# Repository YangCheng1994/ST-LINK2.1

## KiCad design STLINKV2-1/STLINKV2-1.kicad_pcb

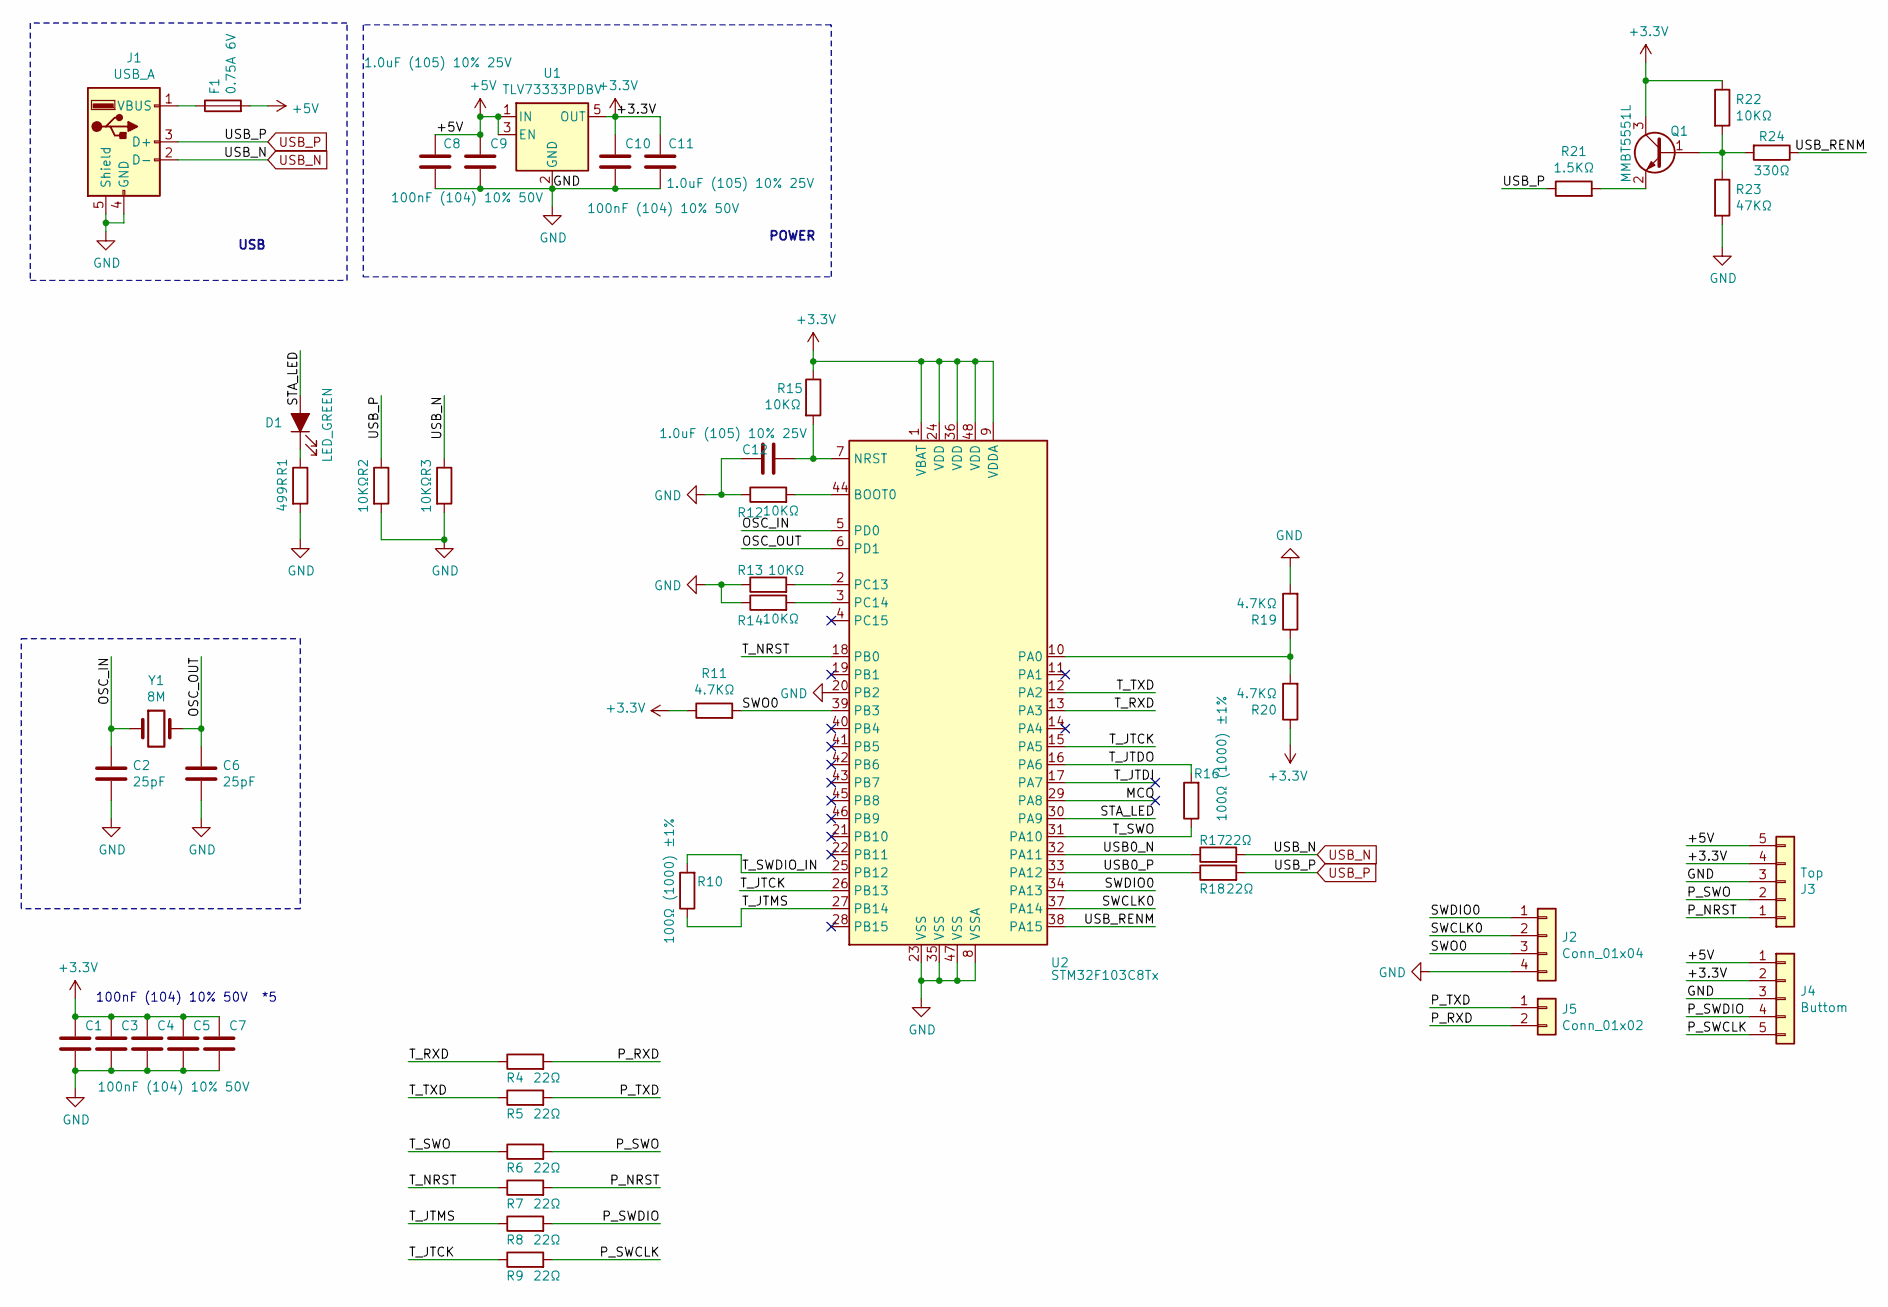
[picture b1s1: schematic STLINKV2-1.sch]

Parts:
C1, C3, C4, C5, C7, C9, C10: 100nF (104) 10% 50V; C_0603_1608Metric
C2, C6: 25pF; C_0603_1608Metric
C8, C11, C12: 1.0uF (105) 10% 25V; C_0603_1608Metric
D1: LED_GREEN; LED_0603_1608Metric
F1: 0.75A 6V; Fuse_0805_2012Metric
J1: USB_A; USB_A_CNCTech_1001-011-01101_Horizontal
J2: Conn_01x04; PinSocket_1x04_P2.54mm_Vertical
J3: Top; Harwin_M20-89005xx_1x05_P2.54mm_Horizontal
J4: Buttom; Harwin_M20-89005xx_1x05_P2.54mm_Horizontal
J5: Conn_01x02; PinSocket_1x02_P2.54mm_Vertical
Q1: MMBT5551L; SOT-23
R1: 499R; R_0603_1608Metric
R2, R3, R12, R13, R14, R15, R22: 10KΩ; R_0603_1608Metric
R4, R5, R6, R7, R8, R9, R17, R18: 22Ω; R_0603_1608Metric
R10, R16: 100Ω (1000) ±1%; R_0603_1608Metric
R11, R19, R20: 4.7KΩ; R_0603_1608Metric
R21: 1.5KΩ; R_0603_1608Metric
R23: 47KΩ; R_0603_1608Metric
R24: 330Ω; R_0603_1608Metric
U1: TLV73333PDBV; SOT-23-5
U2: STM32F103C8Tx; LQFP-48_7x7mm_P0.5mm
Y1: 8M; Oscillator_SMD_TXC_7C-4Pin_5.0x3.2mm

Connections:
+3V3: C1.1, C3.1, C4.1, C5.1, C7.1, C10.1, C11.1, J3.4, J4.2, Q1.3 (C), R11.1, R15.1, R20.1, R22.1, U1.5 (OUT), U2.1 (VBAT), U2.9 (VDDA), U2.24 (VDD), U2.36 (VDD), U2.48 (VDD)
+5V: C8.1, C9.1, F1.2, J3.5, J4.1, U1.1 (IN), U1.3 (EN)
/MCO: U2.29 (PA8)
/OSC_IN: C2.1, U2.5 (PD0), Y1.1, Y1.4
/OSC_OUT: C6.1, U2.6 (PD1), Y1.2, Y1.3
/P_NRST: J3.1, R7.2
/P_RXD: J5.2, R4.2
/P_SWCLK: J4.5, R9.2
/P_SWDIO: J4.4, R8.2
/P_SWO: J3.2, R6.2
/P_TXD: J5.1, R5.2
/STA_LED: D1.2 (A), U2.30 (PA9)
/SWCLK0: J2.2, U2.37 (PA14)
/SWDIO0: J2.1, U2.34 (PA13)
/SWO0: J2.3, R11.2, U2.39 (PB3)
/T_JTCK: R9.1, U2.15 (PA5), U2.26 (PB13)
/T_JTDI: U2.17 (PA7)
/T_JTDO: R16.2, U2.16 (PA6)
/T_JTMS: R8.1, R10.1, U2.27 (PB14)
/T_NRST: R7.1, U2.18 (PB0)
/T_RXD: R4.1, U2.13 (PA3)
/T_SWDIO_IN: R10.2, U2.25 (PB12)
/T_SWO: R6.1, R16.1, U2.31 (PA10)
/T_TXD: R5.1, U2.12 (PA2)
/USB0_N: R17.1, U2.32 (PA11)
/USB0_P: R18.1, U2.33 (PA12)
/USB_RENM: R24.1, U2.38 (PA15)
GND: C1.2, C2.2, C3.2, C4.2, C5.2, C6.2, C7.2, C8.2, C9.2, C10.2, C11.2, C12.2, J1.4 (GND), J1.5 (Shield), J2.4, J3.3, J4.3, R1.2, R2.2, R3.2, R12.1, R13.1, R14.1, R19.2, R23.2, U1.2 (GND), U2.8 (VSSA), U2.20 (PB2), U2.23 (VSS), U2.35 (VSS), U2.47 (VSS)
unnamed: C12.1, R15.2, U2.7 (NRST)
unnamed: D1.1 (K), R1.1
unnamed: F1.1, J1.1 (VBUS)
unnamed: Q1.1 (B), R22.2, R23.1, R24.2
unnamed: Q1.2 (E), R21.2
unnamed: R12.2, U2.44 (BOOT0)
unnamed: R13.2, U2.2 (PC13)
unnamed: R14.2, U2.3 (PC14)
unnamed: R19.1, R20.2, U2.10 (PA0)
USB_N: J1.2 (D-), R3.1, R17.2
USB_P: J1.3 (D+), R2.1, R18.2, R21.1

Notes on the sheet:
USB
POWER
100nF (104) 10% 50V *5

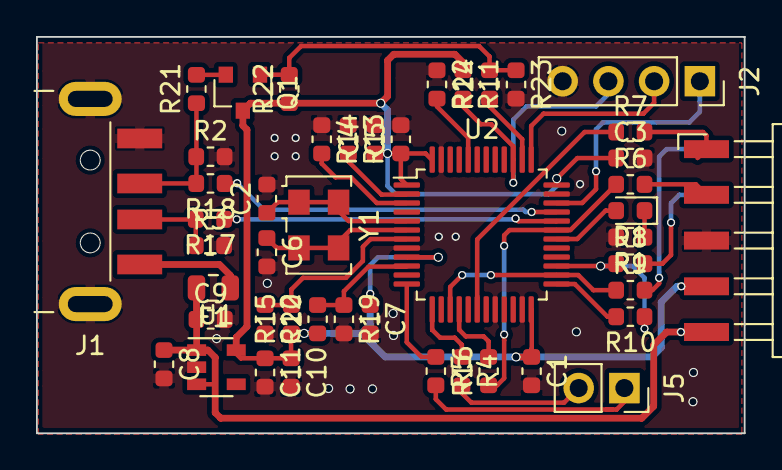
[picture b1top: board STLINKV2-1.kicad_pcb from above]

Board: 2 copper layers, 39.3 x 22.0 mm, 47 parts (1 on the bottom side), 37 nets.

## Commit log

2019-12-02 basic
2019-12-02 layout 基本完成
2019-12-02 layout finished
